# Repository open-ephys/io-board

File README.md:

I/O Board
========

Description
-----------------
Need to sync your neural data with external triggers? Use this board to connect up to 8 digital inputs to the acquisition board. Since its internal components are completely passive, the I/O board can be also be used to relay digital outputs and analog inputs.

Time to build: 1 hour

View on [Open Ephys](https://open-ephys.org/acquisition-system/io-board-pcb)

If you're interested in building your own I/O Board, we strongly recommend getting in touch with us via the Open Ephys [contact](http://open-ephys.com/contact) page.

Specifications
-------------------
- 8 vertical BNC terminals
- HDMI type A connector

Ordering info
-------------------
4.9" x 3.6"

File types:
--------------
- .ai = Adobe Illustrator files; contain images of hardware
- .brd = EAGLE board files; describe the physical layout of the printed circuit board
- .sch = EAGLE schematic files; describe the electrical connections of the printed circuit board
- .cam = EAGLE export files; contain instructions for translating between the .brd file and Gerber files
- BOM.txt = Bill of Materials; contains part numbers for all components (from DigiKey unless otherwise specified)
- .md = Markdown files; most likely a README file; can be viewed with any text edtior
- "gerber" files (.top, .bsk, .oln, etc.) = contain machine-readable instructions for creating the printed circuit board; these are sent to a fab house (such as Sunstone Circuits) for PCB production
- .SLDPRT files = SolidWorks part files; contain CAD models of 3D components
- .STL files = stereolithography files; can be sent to a rapid prototyping service (such as Shapeways) to create 3D objects
- .eps file = encapsulated postscript files; describe the shape of laser-cut parts (Ponoko only). Can be edited in Adobe Illustrator.

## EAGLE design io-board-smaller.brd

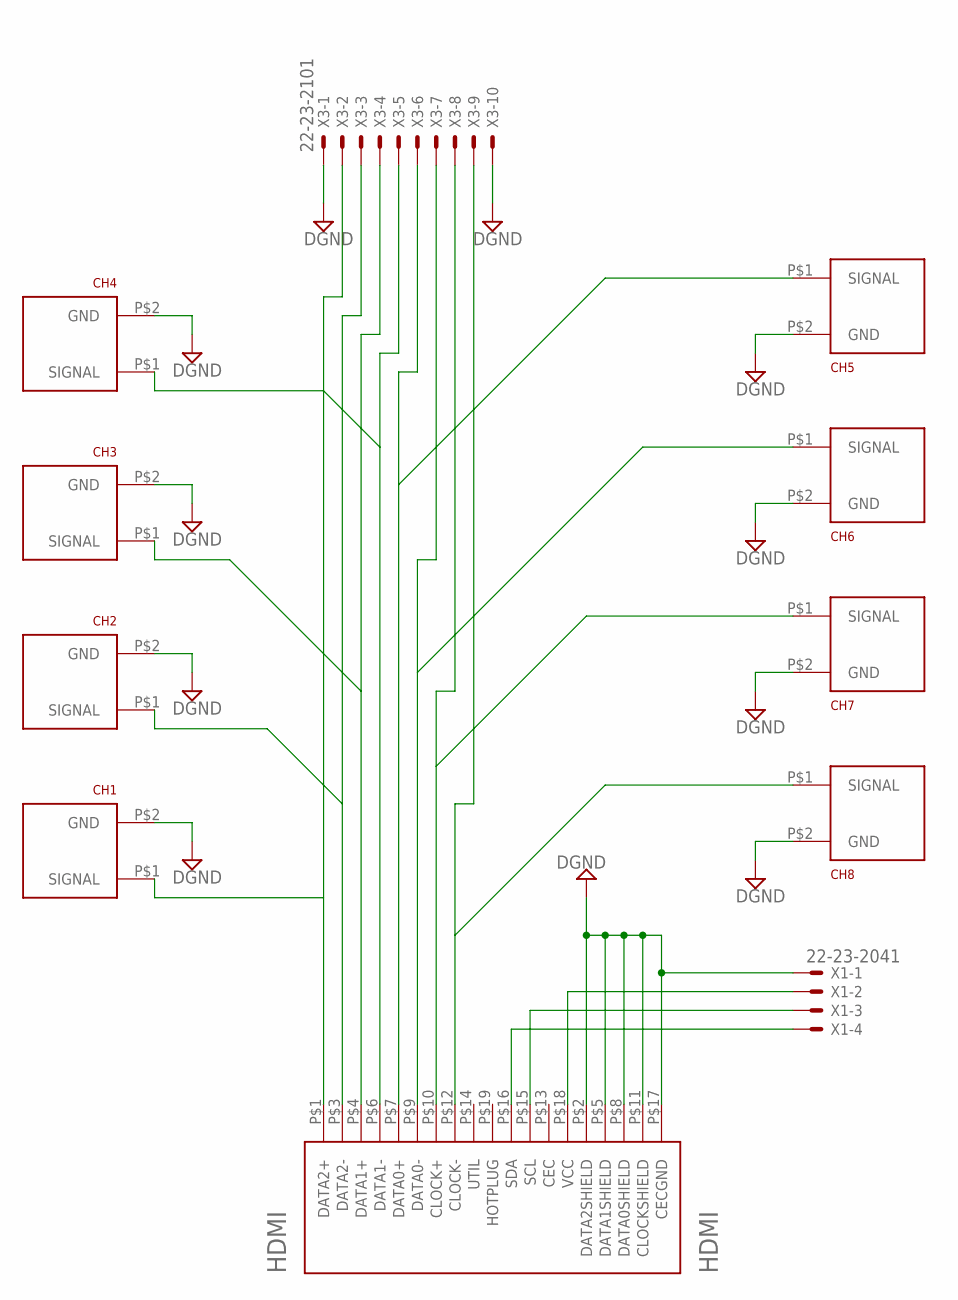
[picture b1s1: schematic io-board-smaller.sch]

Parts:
CH1, CH2, CH3, CH4, CH5, CH6, CH7, CH8: BNC_VERTICAL
HDMI: HDMI; HDMI_A
X1: 22-23-2041
X3: 22-23-2101

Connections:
CH6: CH6.P$1 (SIGNAL), HDMI.P$9 (DATA0-), X3.7
DGND: CH1.P$2 (GND), CH2.P$2 (GND), CH3.P$2 (GND), CH4.P$2 (GND), CH5.P$2 (GND), CH6.P$2 (GND), CH7.P$2 (GND), CH8.P$2 (GND), HDMI.P$2 (DATA2SHIELD), HDMI.P$5 (DATA1SHIELD), HDMI.P$8 (DATA0SHIELD), HDMI.P$11 (CLOCKSHIELD), HDMI.P$17 (CECGND), X1.1, X3.1, X3.10
I2C_CLK: HDMI.P$15 (SCL), X1.3
I2C_DAT: HDMI.P$16 (SDA), X1.4
unnamed: CH3.P$1 (SIGNAL), HDMI.P$4 (DATA1+), X3.4
unnamed: CH2.P$1 (SIGNAL), HDMI.P$3 (DATA2-), X3.3
unnamed: CH1.P$1 (SIGNAL), HDMI.P$1 (DATA2+), X3.2
unnamed: CH5.P$1 (SIGNAL), HDMI.P$7 (DATA0+), X3.6
unnamed: CH7.P$1 (SIGNAL), HDMI.P$10 (CLOCK+), X3.8
unnamed: CH8.P$1 (SIGNAL), HDMI.P$12 (CLOCK-), X3.9
unnamed: CH4.P$1 (SIGNAL), HDMI.P$6 (DATA1-), X3.5
VCC: HDMI.P$18 (VCC), X1.2

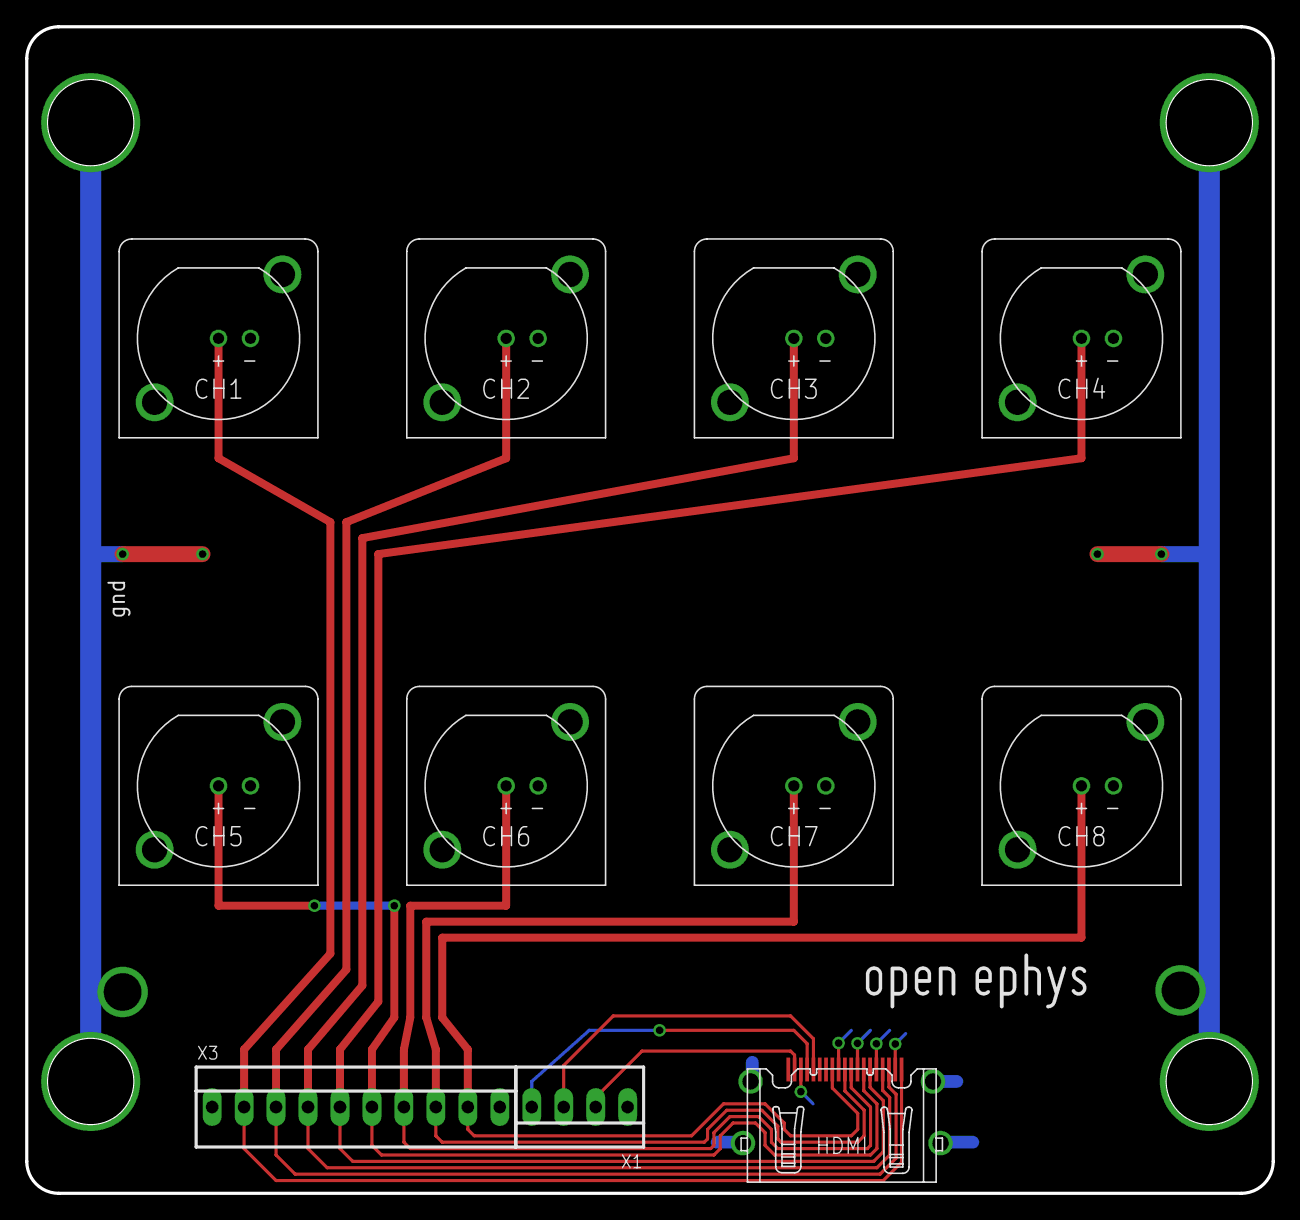
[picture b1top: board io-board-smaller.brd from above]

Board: 2 copper layers, 99.1 x 92.7 mm, 12 parts (0 on the bottom side), 12 nets.

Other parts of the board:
U$2: OPEN_EPHYS_LOGO

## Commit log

2012-08-31 Added case files
2012-08-31 Added license files
2012-09-01 Removed holes from board cover
2012-09-19 Updated README file
2013-03-19 added draft for rack-mounted 4x io panel
2013-03-22 changed rackmounted IO board to single 8ch board
    to be used with laser-cut mounting panel, or on its own
    added pin headers for i2c and channels
2013-04-07 Minor changes
2013-05-07 updated .1 inch connector to be linear
2013-05-26 Remove LEDs
2013-05-26 Redo rounting
2013-05-26 Minor fixes
2013-07-30 hole pattern now fits 19" rack
    changed spacing to 0.625, 0.625, 0.5, 0.625, 0.625
2013-07-30 OS X changes
2013-07-30 Restore large holes and add 3 mm holes for mounting a case
2013-07-30 Make rackmount board the default
2013-07-30 Update README file
2013-07-31 Add new Gerber files
2013-07-31 Add CAM file
2013-07-31 Add DXF file
2013-07-31 Add Illustrator file
2013-07-31 Add png file
2013-08-01 Reverse order of numbers on screw terminals
2013-08-16 Added designs in which IO Board fits within a 10 cm x 10 cm box. Helpful for Fusion PCB service.
2014-07-16 Add images of bare and populated board
2021-12-09 Update README.md
    Fix broken link
2024-09-30 Add PDF of schematic
